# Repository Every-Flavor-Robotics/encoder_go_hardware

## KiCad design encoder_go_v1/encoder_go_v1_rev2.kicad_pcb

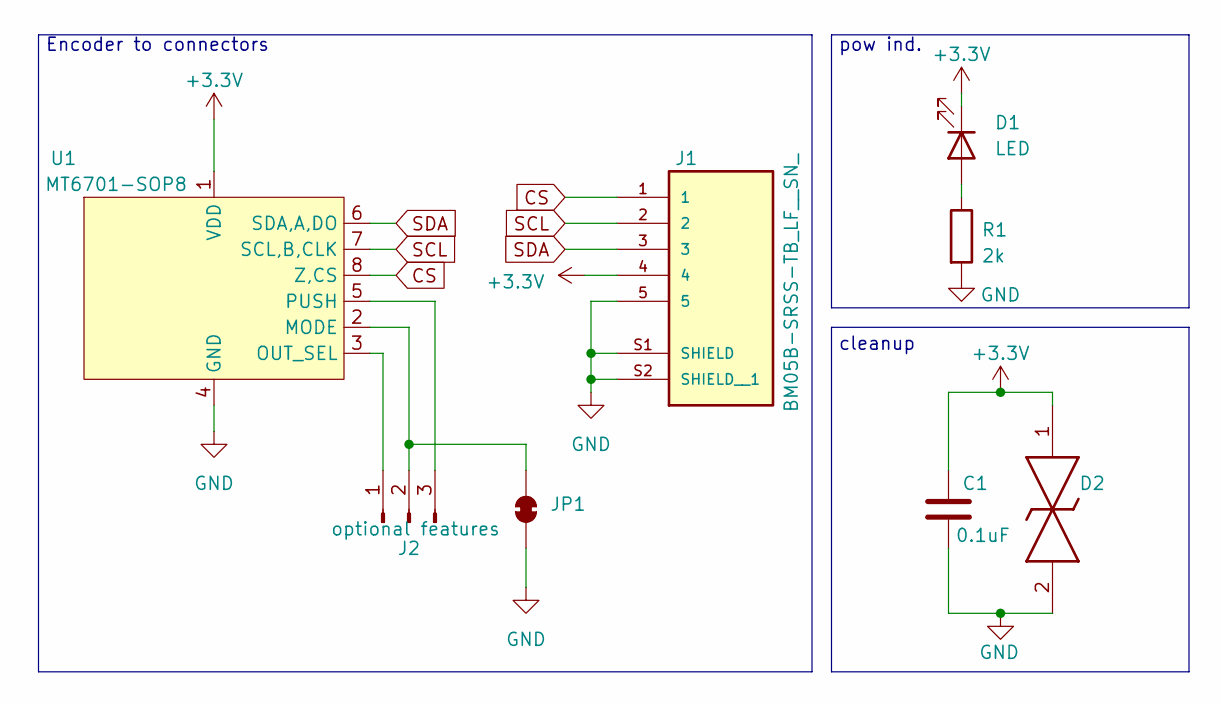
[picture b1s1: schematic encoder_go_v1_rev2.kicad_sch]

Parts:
C1: 0.1uF; C_0805_2012Metric_Pad1.18x1.45mm_HandSolder
D1: LED; D_0805_2012Metric
D2: SMAJ6.0CAe3_TR13; DIONM5025X225N; Mouser Part Number 494-SMAJ6.0CAE3/TR13
J1: BM05B-SRSS-TB_LF__SN_; JST_BM05B-SRSS-TB_LF__SN_; PARTREV N/A
J2: optional features; PinHeader_1x03_P2.54mm_Horizontal
JP1: SolderJumper_2_Bridged; SolderJumper-2_P1.3mm_Bridged_RoundedPad1.0x1.5mm
R1: 2k; R_0805_2012Metric_Pad1.20x1.40mm_HandSolder
U1: MT6701-SOP8; MT6701_SOP8

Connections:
+3.3V: C1.1, D1.1 (K), D2.1, J1.4, U1.1 (VDD)
CS: J1.1, U1.8 (Z,CS)
GND: C1.2, D2.2, J1.5, J1.S1 (SHIELD), J1.S2 (SHIELD__1), JP1.1 (A), R1.2, U1.4 (GND)
unnamed: D1.2 (A), R1.1
unnamed: J2.1, U1.3 (OUT_SEL)
unnamed: J2.2, JP1.2 (B), U1.2 (MODE)
unnamed: J2.3, U1.5 (PUSH)
SCL: J1.2, U1.7 (SCL,B,CLK)
SDA: J1.3, U1.6 (SDA,A,DO)

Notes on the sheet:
pow ind.
Encoder to connectors
cleanup

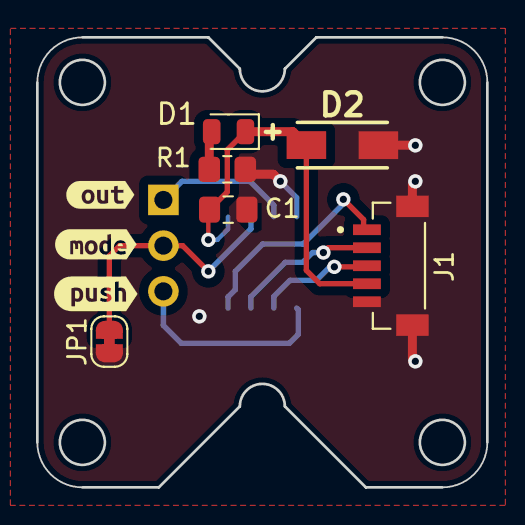
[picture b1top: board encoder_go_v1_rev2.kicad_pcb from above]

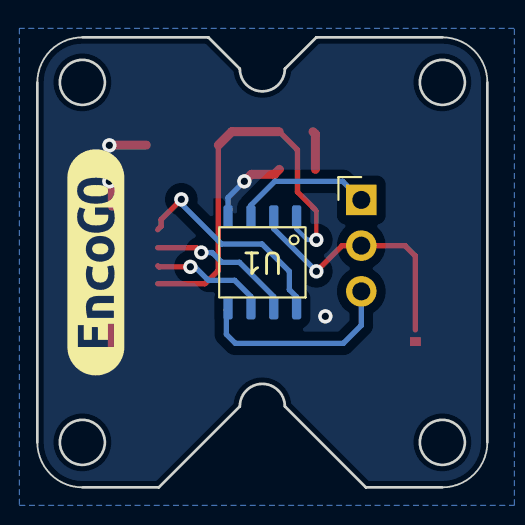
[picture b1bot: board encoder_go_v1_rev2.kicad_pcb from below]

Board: 2 copper layers, 25.0 x 25.0 mm, 12 parts (3 on the bottom side), 9 nets.

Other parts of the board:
kibuzzard-69442F0D: G***; kibuzzard-69442F0D
kibuzzard-69442F26: G***; kibuzzard-69442F26
kibuzzard-69442F34: G***; kibuzzard-69442F34
kibuzzard-69640B5A: G***; kibuzzard-69640B5A

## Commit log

2026-01-11 remove unused files and edited pcb for cnc mill process
2026-01-11 adjust silkscreen
